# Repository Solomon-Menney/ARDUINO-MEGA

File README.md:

## 📌 Project Overview

The **Custom Arduino Mega** is an open-source hardware project developed as a custom implementation of the Arduino Mega platform.

The board is suitable for:

* Embedded systems development
* Robotics projects
* Automation and control systems
* IoT applications
* Sensor interfacing
* Motor control
* Electronics prototyping
* Academic and engineering projects

---

## ✨ Features

* ATmega2560 microcontroller
* Arduino Mega-compatible architecture
* Digital I/O pins
* Analog input pins
* PWM outputs
* UART serial communication
* SPI communication
* I²C communication
* USB programming/communication interface
* External power input
* On-board voltage regulation
* Reset circuit
* ICSP programming interface
* Power and status indicators
* Standard Arduino-style headers

---

## 🔧 Main Specifications

| Parameter           | Specification  |
| ------------------- | -------------- |
| Microcontroller     | ATmega2560     |
| Architecture        | 8-bit AVR      |
| Operating Voltage   | 5 V            |
| Digital I/O         | 54             |
| PWM Outputs         | 15             |
| Analog Inputs       | 16             |
| UART Ports          | 4              |
| Communication       | UART, SPI, I²C |
| Clock Frequency     | 16 MHz         |
| Programming         | USB / ICSP     |
| PCB Design Software | KiCad          |
| Board Type          | Custom PCB     |

---

## 🧠 Microcontroller

The main controller used on the board is the **ATmega2560**.

The microcontroller provides a large number of digital and analog I/O pins, making the board suitable for projects that require more pins than a standard Arduino Uno.

### ATmega2560 Functions

* Digital input/output
* Analog-to-digital conversion
* PWM generation
* Hardware timers
* UART communication
* SPI communication
* I²C communication
* External interrupts
* Flash, SRAM and EEPROM memory

---

## 🔌 Communication Interfaces

The board supports several communication protocols.

### UART

The ATmega2560 provides four hardware serial interfaces:

* Serial0
* Serial1
* Serial2
* Serial3

These can be used to communicate with:

* GPS modules
* GSM modules
* Bluetooth modules
* Other microcontrollers
* Computers

### I²C

I²C can be used to connect devices such as:

* Sensors
* LCD displays
* RTC modules
* EEPROMs
* I/O expanders

### SPI

SPI can be used for high-speed communication with:

* SD cards
* Displays
* Sensors
* Flash memory
* Other SPI devices

---

## ⚡ Power Supply

The board contains a dedicated power section for supplying the required voltage to the microcontroller and other circuits.

Possible power sources include:

* USB
* External DC input

The power section includes:

* Voltage regulation
* Power filtering
* Decoupling capacitors
* Reverse-polarity protection *(if implemented)*
* Power indicator LED

> **Note:** Verify the exact input-voltage range of your implemented power circuit before connecting an external supply.

---

## 🔄 Reset Circuit

A reset circuit is included to allow the ATmega2560 to restart and enter the bootloader/programming process.

The reset circuit consists of components such as:

* Reset push button
* Pull-up resistor
* Reset capacitor *(depending on the design)*

---

## 💻 Programming

The board can be programmed using the Arduino IDE or another compatible AVR development environment.

### Arduino IDE

1. Install the Arduino IDE.
2. Connect the board to a computer through USB.
3. Select the appropriate board configuration.
4. Select the correct COM port.
5. Upload your Arduino program.

For a Mega-compatible configuration, select:

**Tools → Board → Arduino Mega or Mega 2560**

Then select the appropriate processor option for your hardware.

## 🖥️ PCB Design

The PCB was designed using **KiCad**.

The project includes the following design files:

```text
Custom-Arduino-Mega/
│
├── README.md
│
├── Schematic/
│   └── Arduino_Mega.kicad_sch
│
├── PCB/
│   └── Arduino_Mega.kicad_pcb
│
├── Gerber/
│   └── Manufacturing_Files/
│
├── 3D/
│   └── PCB_3D_View/
│
└── Documentation/
    ├── Pinout/
    └── Images/
```

---

## 📐 Design Files

The repository contains:

* KiCad schematic
* KiCad PCB layout
* Gerber files
* Drill files
* Bill of Materials (BOM)
* Component datasheets
* Firmware/test programs
* PCB renders
* Project documentation

---

## 🧾 Bill of Materials

| Component          | Description                   |    Quantity |
| ------------------ | ----------------------------- | ----------: |
| ATmega2560         | Main microcontroller          |           1 |
| USB Interface      | USB communication/programming |           1 |
| Voltage Regulator  | 5 V regulation                |           1 |
| Crystal/Oscillator | 16 MHz clock                  |           1 |
| Capacitors         | Power/decoupling              |     Several |
| Resistors          | Pull-up/current limiting      |     Several |
| LEDs               | Power/status indicators       |     Several |
| Push Button        | Reset                         |           1 |
| Pin Headers        | I/O connections               |     Several |
| Diodes             | Protection                    | As required |

> The exact component values and part numbers are provided in the project schematic and BOM.

---

## 📷 Project Images

Add your project images here.

### Schematic

### PCB Layout

### 3D PCB View

This custom Arduino Mega board can be used in:

* Industrial automation
* Robotics
* Smart home systems
* IoT systems
* Solar energy systems
* Motor control
* Sensor networks
* Data acquisition
* Embedded control systems
* Engineering research and education

---

## 🛠️ Tools Used

### Hardware Design

* KiCad
* ATmega2560 datasheet
* AVR documentation

### Software

* Arduino IDE
* AVR toolchain

### Manufacturing

* PCB fabrication service
* Soldering and assembly tools

---

Documentation

Important documents are included in the `Documentation` directory.

These may include:

* Circuit schematic
* PCB layout
* Pinout diagram
* Datasheets
* BOM
* Design calculations
* Assembly information
* Testing results

---

Recommended Tests

* [ ] Visual inspection
* [ ] Check for PCB shorts
* [ ] Verify power input
* [ ] Verify regulated voltage
* [ ] Test reset circuit
* [ ] Test USB communication
* [ ] Test microcontroller programming
* [ ] Test digital I/O
* [ ] Test analog inputs
* [ ] Test UART
* [ ] Test I²C
* [ ] Test SPI

---

## 📈 Future Improvements

Possible future improvements include:

* Improved power protection
* USB-C connector
* Additional power monitoring
* Battery input
* Reverse-polarity protection
* ESD protection
* Improved PCB layout
* Additional status indicators
* More expansion connectors
* Improved thermal management

---

 Author
SOLOMON MENNEY
Electrical/Electronic Engineering Student
Accra Technical University

**Built with KiCad, AVR technology, and a passion for embedded systems.**

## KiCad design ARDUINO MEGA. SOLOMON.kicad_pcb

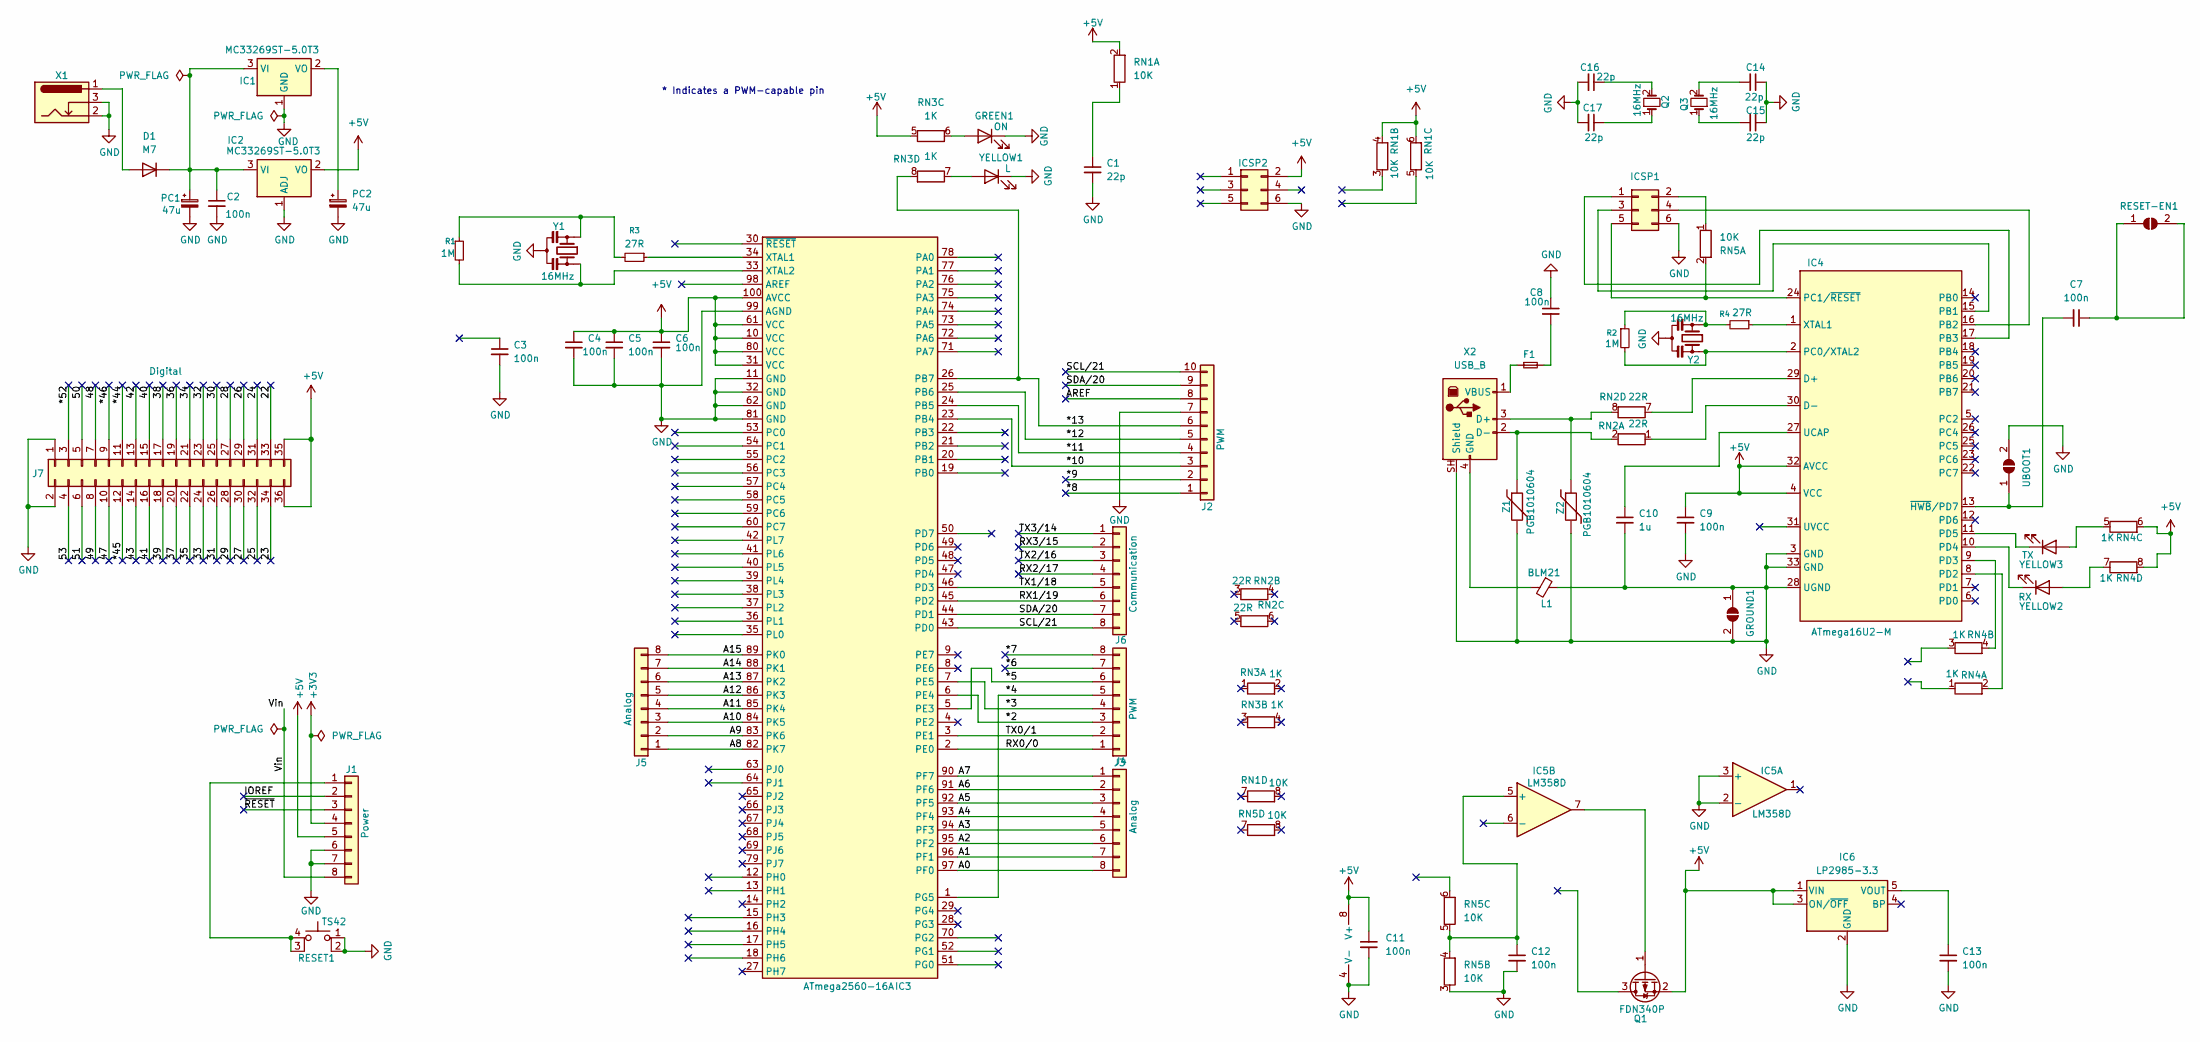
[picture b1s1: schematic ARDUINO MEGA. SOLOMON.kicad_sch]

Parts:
C1, C14, C15, C16, C17: 22p; C_0805_2012Metric
C2, C3, C4, C5, C6, C7, C8, C9, C11, C12, C13: 100n; C_0805_2012Metric
C10: 1u; C_0805_2012Metric
D1: M7; D_SMA
F1: 500mA; Fuse_1812_4532Metric
GREEN1: ON; LED_0805_2012Metric
GROUND1: SolderJumper_2_Open; SolderJumper-2_P1.3mm_Bridged_Pad1.0x1.5mm
IC1, IC2: MC33269ST-5.0T3; SOT-223-3_TabPin2
IC3: ATmega2560-16A; TQFP-100_14x14mm_P0.5mm
IC4: ATmega16U2-M; QFN-32-1EP_5x5mm_P0.5mm_EP3.1x3.1mm
IC5: LM358D; SOIC-8_3.9x4.9mm_P1.27mm
IC6: LP2985-3.3; SOT-23-5
ICSP1, ICSP2: Conn_02x03_Odd_Even; PinHeader_2x03_P2.54mm_Vertical
J1: Power; PinSocket_1x08_P2.54mm_Vertical
J2: PWM; PinSocket_1x10_P2.54mm_Vertical
J3, J5: Analog; PinSocket_1x08_P2.54mm_Vertical
J4: PWM; PinSocket_1x08_P2.54mm_Vertical
J6: Communication; PinSocket_1x08_P2.54mm_Vertical
J7: Digital; PinSocket_2x18_P2.54mm_Vertical
L1: BLM21; L_0805_2012Metric
PC1, PC2: 47u; CP_Elec_6.3x5.4
Q1: FDN340P; SOT-23
Q2, Q3: 16MHz; Crystal_SMD_5032-2Pin_5.0x3.2mm
R1, R2: 1M; R_0805_2012Metric
R3, R4: 27R; R_0805_2012Metric
RESET1: TS42; SW_SPST_PTS645Sx43SMTR92
RESET-EN1: SolderJumper_2_Open; SolderJumper-2_P1.3mm_Bridged_Pad1.0x1.5mm
RN1, RN5: 10K; R_Array_Convex_4x0603
RN2: 22R; R_Array_Convex_4x0603
RN3, RN4: 1K; R_Array_Convex_4x0603
UBOOT1: SolderJumper_2_Open; SolderJumper-2_P1.3mm_Bridged_Pad1.0x1.5mm
X1: Barrel_Jack_Switch; BarrelJack_Horizontal
X2: USB_B; USB_B_OST_USB-B1HSxx_Horizontal
Y1: 16MHz; Crystal_SMD_HC49-SD
Y2: 16MHz; Resonator_SMD_Murata_CSTxExxV-3Pin_3.0x1.1mm
YELLOW1: L; LED_0805_2012Metric
YELLOW2: RX; LED_0805_2012Metric
YELLOW3: TX; LED_0805_2012Metric
Z1, Z2: PGB1010604; R_0603_1608Metric

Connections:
+3V3: J1.4
+5V: C4.1, C5.1, C6.1, C9.1, C11.1, IC2.2 (VO), IC3.10 (VCC), IC3.31 (VCC), IC3.61 (VCC), IC3.80 (VCC), IC3.100 (AVCC), IC4.4 (VCC), IC4.32 (AVCC), IC5.8 (V+), IC6.1 (VIN), IC6.3 (ON/~OFF), ICSP2.2, J1.5, J7.35, J7.36, Q1.2 (S), RN1.2 (R1.2), RN1.4 (R2.2), RN1.6 (R3.2), RN3.5 (R3.1), RN4.6 (R3.2), RN4.8 (R4.2)
/22: J7.33
/23: J7.34
/24: J7.31
/25: J7.32
/26: J7.29
/27: J7.30
/28: J7.27
/29: J7.28
/30: J7.25
/31: J7.26
/32: J7.23
/33: J7.24
/34: J7.21
/35: J7.22
/36: J7.19
/37: J7.20
/38: J7.17
/39: J7.18
/40: J7.15
/41: J7.16
/42: J7.13
/43: J7.14
/47: J7.10
/48: J7.7
/49: J7.8
/50: J7.5
/51: J7.6
/53: J7.4
/*2: IC3.6 (PE4), J4.3
/*3: IC3.7 (PE5), J4.4
/*4: IC3.1 (PG5), J4.5
/*5: IC3.5 (PE3), J4.6
/*6: J4.7
/*7: J4.8
/*8: J2.1
/*9: J2.2
/*10: IC3.23 (PB4), J2.3
/*11: IC3.24 (PB5), J2.4
/*12: IC3.25 (PB6), J2.5
/*13: IC3.26 (PB7), J2.6, RN3.8 (R4.2)
/*44: J7.11
/*45: J7.12
/*46: J7.9
/*52: J7.3
/A0: IC3.97 (PF0), J3.8
/A1: IC3.96 (PF1), J3.7
/A2: IC3.95 (PF2), J3.6
/A3: IC3.94 (PF3), J3.5
/A4: IC3.93 (PF4), J3.4
/A5: IC3.92 (PF5), J3.3
/A6: IC3.91 (PF6), J3.2
/A7: IC3.90 (PF7), J3.1
/A8: IC3.82 (PK7), J5.1
/A9: IC3.83 (PK6), J5.2
/A10: IC3.84 (PK5), J5.3
/A11: IC3.85 (PK4), J5.4
/A12: IC3.86 (PK3), J5.5
/A13: IC3.87 (PK2), J5.6
/A14: IC3.88 (PK1), J5.7
/A15: IC3.89 (PK0), J5.8
/AREF: J2.8
/IOREF: J1.2
/RX0/0: IC3.2 (PE0), J4.1
/RX1/19: IC3.45 (PD2), J6.6
/RX2/17: J6.4
/RX3/15: J6.2
/SCL/21: IC3.43 (PD0), J2.10, J6.8
/SDA/20: IC3.44 (PD1), J2.9, J6.7
/TX0/1: IC3.3 (PE1), J4.2
/TX1/18: IC3.46 (PD3), J6.5
/TX2/16: J6.3
/TX3/14: J6.1
/Vin: J1.8
/~RESET: J1.3
GND: C1.2, C2.2, C3.2, C4.2, C5.2, C6.2, C8.1, C9.2, C10.2, C11.2, C12.2, C13.2, C14.1, C15.1, C16.2, C17.2, GREEN1.1 (K), GROUND1.1 (A), GROUND1.2 (B), IC1.1 (GND), IC2.1 (ADJ), IC3.11 (GND), IC3.32 (GND), IC3.62 (GND), IC3.81 (GND), IC3.99 (AGND), IC4.3 (GND), IC4.28 (UGND), IC4.33 (GND), IC5.2 (-), IC5.3 (+), IC5.4 (V-), IC6.2 (GND), ICSP1.6, ICSP2.6, J1.6, J1.7, J2.7, J7.1, J7.2, L1.1, PC1.2, PC2.2, RESET1.1, RESET1.2, RN5.3 (R2.1), UBOOT1.2 (B), X1.2, X1.3, X2.SH (Shield), Y1.2, Y2.2, YELLOW1.1 (K), Z1.2, Z2.2
unnamed: C8.2, F1.2
unnamed: C14.2, Q3.2
unnamed: C15.2, Q3.1
unnamed: C16.1, Q2.2
unnamed: C17.1, Q2.1
unnamed: D1.2 (A), X1.1
unnamed: C2.1, D1.1 (K), IC1.3 (VI), IC2.3 (VI), PC1.1
unnamed: GREEN1.2 (A), RN3.6 (R3.2)
unnamed: IC1.2 (VO), PC2.1
unnamed: IC3.34 (XTAL1), R3.1
unnamed: IC3.33 (XTAL2), R1.2, Y1.3
unnamed: IC4.29 (D+), RN2.7 (R4.1)
unnamed: IC4.30 (D-), RN2.1 (R1.1)
unnamed: IC4.15 (PB1), ICSP1.3
unnamed: IC4.16 (PB2), ICSP1.4
unnamed: IC4.17 (PB3), ICSP1.1
unnamed: IC4.2 (PC0/XTAL2), R2.2, Y2.3
unnamed: IC4.24 (PC1/~RESET), ICSP1.5, RN5.2 (R1.2)
unnamed: IC4.8 (PD2), RN4.2 (R1.2)
unnamed: IC4.9 (PD3), RN4.4 (R2.2)
unnamed: IC4.10 (PD4), YELLOW2.1 (K)
unnamed: IC4.11 (PD5), YELLOW3.1 (K)
unnamed: C10.1, IC4.27 (UCAP)
unnamed: IC4.1 (XTAL1), R4.1
unnamed: C7.2, IC4.13 (~HWB/PD7), UBOOT1.1 (A)
unnamed: C12.1, IC5.5 (+), RN5.4 (R2.2), RN5.5 (R3.1)
unnamed: C13.1, IC6.5 (VOUT)
unnamed: ICSP1.2, RN5.1 (R1.1)
unnamed: J1.1, RESET1.3 (K), RESET1.4 (A)
unnamed: IC5.7, Q1.1 (G)
unnamed: R1.1, R3.2, Y1.1
unnamed: R2.1, R4.2, Y2.1
unnamed: C7.1, RESET-EN1.1 (A), RESET-EN1.2 (B)
unnamed: C1.1, RN1.1 (R1.1)
unnamed: RN2.2 (R1.2), X2.2 (D-), Z1.1
unnamed: RN2.8 (R4.2), X2.3 (D+), Z2.1
unnamed: RN3.7 (R4.1), YELLOW1.2 (A)
unnamed: RN4.5 (R3.1), YELLOW3.2 (A)
unnamed: RN4.7 (R4.1), YELLOW2.2 (A)
unnamed: L1.2, X2.4 (GND)
unnamed: F1.1, X2.1 (VBUS)

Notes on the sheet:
* Indicates a PWM-capable pin

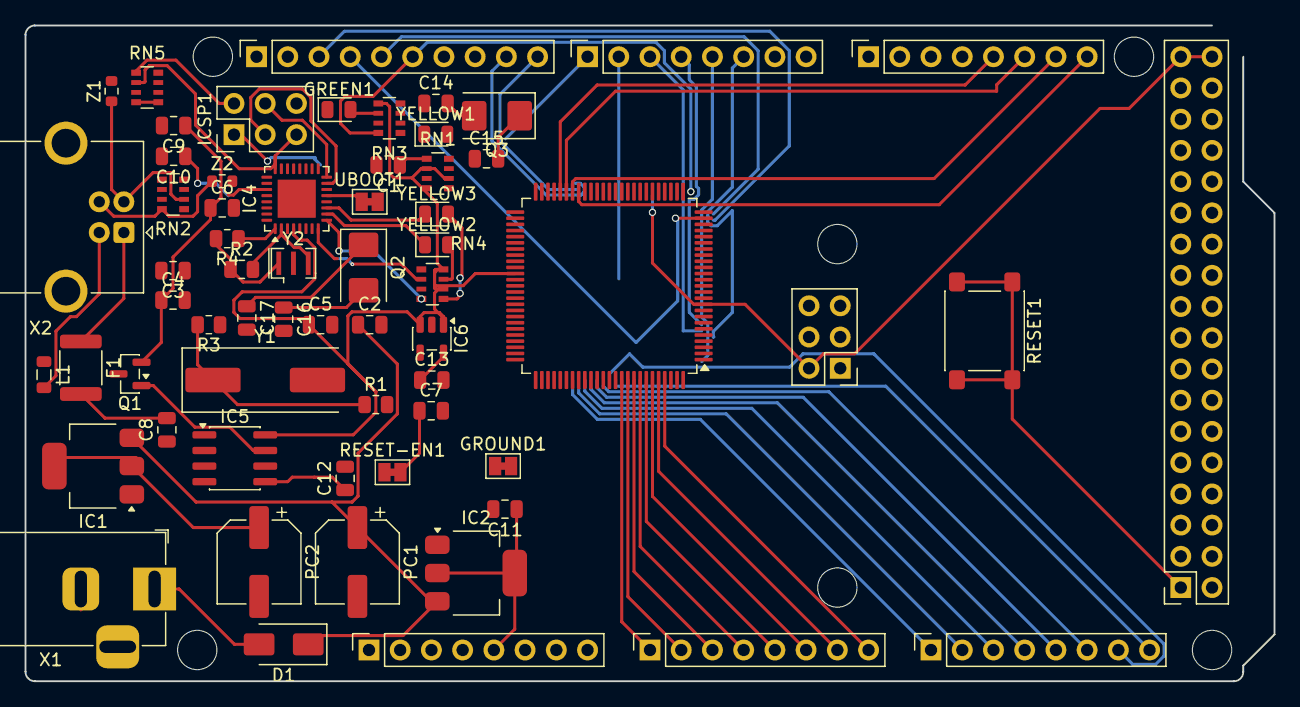
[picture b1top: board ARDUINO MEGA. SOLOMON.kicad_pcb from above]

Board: 2 copper layers, 101.6 x 53.3 mm, 69 parts (0 on the bottom side), 72 nets.

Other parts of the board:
MH1, MH2, MH3, MH4, MH5, MH6: MountingHole_3.2mm
